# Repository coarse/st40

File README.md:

# ST40 PCB

No frills, open source 40% ortholinear keyboard PCB

## Specs

- Planck-like layout
- South-facing LED (even though there is no backlight) because that's how switches were meant to be oriented
- No backlight, no underglow
- No fancy ESD protection
- No fancy reset circuit
- USB Mini because literally no frills
- STM32F072CBT6

## Requirements

- KiCad 5.0.1
- Default KiCad Schematic Library
- ai03's Switch Footprint Library (included as submodule)

## Notes

1. To be used as a reference for STM32F072CBT6 only
2. Can't guarantee that this PCB is compatible with Planck cases

## Questions?

 - Hit me up on Discord (Miyo#2210) or via e-mail (mfmayol@up.edu.ph)
 
## License

The design is licensed under [CC BY-SA 4.0](https://creativecommons.org/licenses/by-sa/4.0/).

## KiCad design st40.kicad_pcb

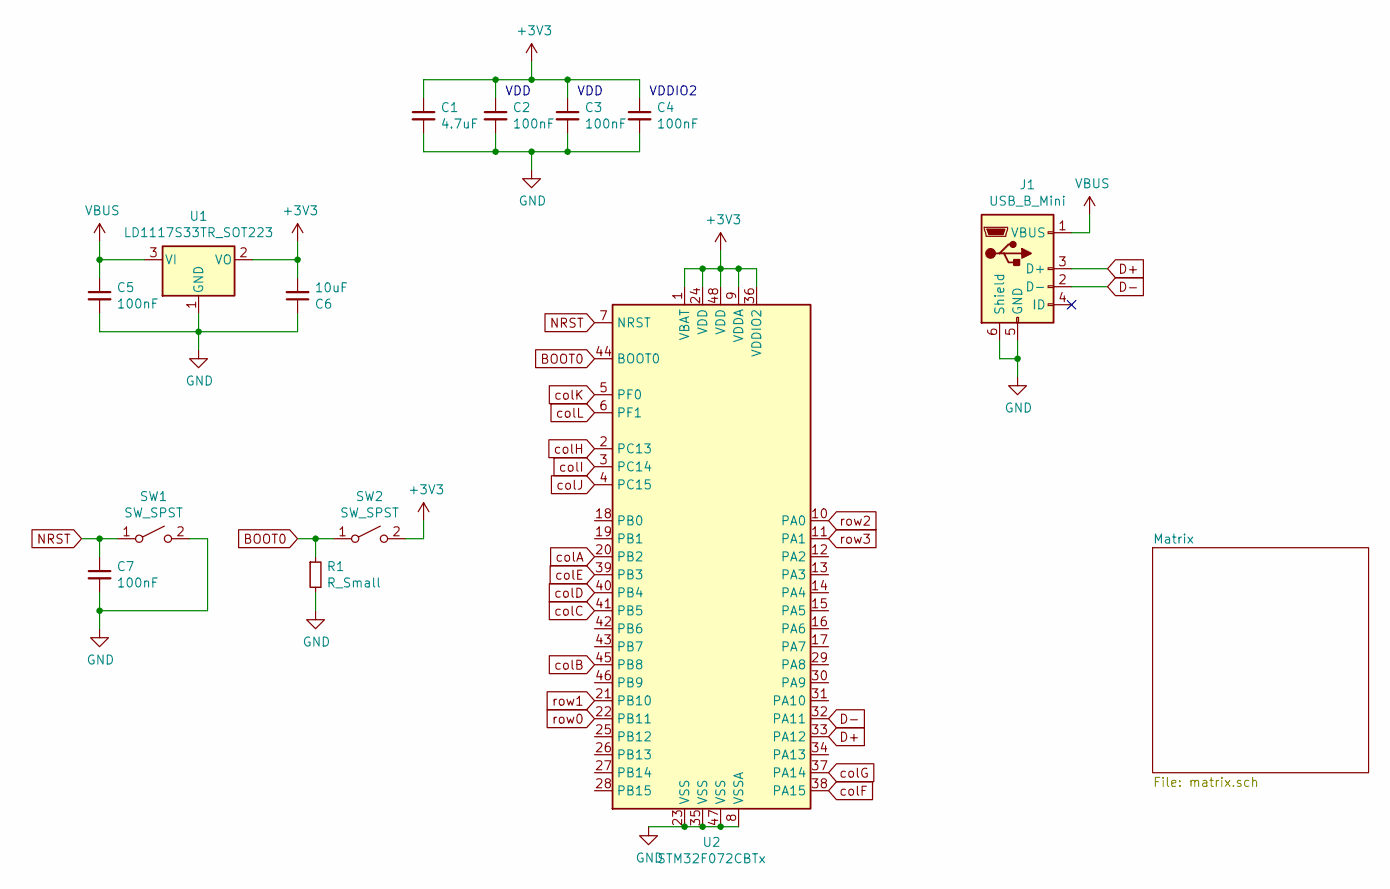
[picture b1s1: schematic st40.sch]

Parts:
C1: 4.7uF; C_0603_1608Metric_Pad1.05x0.95mm_HandSolder
C2, C3, C4, C5, C7: 100nF; C_0603_1608Metric_Pad1.05x0.95mm_HandSolder
C6: 10uF; C_0603_1608Metric_Pad1.05x0.95mm_HandSolder
J1: USB_B_Mini; USB-Mini-B_ LCSC-C46398
R1: R_Small; R_0603_1608Metric_Pad1.05x0.95mm_HandSolder
SW1, SW2: SW_SPST; SW_PUSH_6mm
U1: LD1117S33TR_SOT223; SOT-223
U2: STM32F072CBTx; LQFP-48_7x7mm_P0.5mm

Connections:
+3V3: C1.1, C2.1, C3.1, C4.1, C6.2, SW2.2 (B), U1.2 (VO), U2.1 (VBAT), U2.9 (VDDA), U2.24 (VDD), U2.36 (VDDIO2), U2.48 (VDD)
BOOT0: R1.1, SW2.1 (A), U2.44 (BOOT0)
D+: J1.3 (D+), U2.33 (PA12)
D-: J1.2 (D-), U2.32 (PA11)
GND: C1.2, C2.2, C3.2, C4.2, C5.2, C6.1, C7.2, J1.5 (GND), J1.6 (Shield), R1.2, SW1.2 (B), U1.1 (GND), U2.8 (VSSA), U2.23 (VSS), U2.35 (VSS), U2.47 (VSS)
NRST: C7.1, SW1.1 (A), U2.7 (NRST)
VBUS: C5.1, J1.1 (VBUS), U1.3 (VI)
colA: U2.20 (PB2); also elsewhere on the board
colB: U2.45 (PB8); also elsewhere on the board
colC: U2.41 (PB5); also elsewhere on the board
colD: U2.40 (PB4); also elsewhere on the board
colE: U2.39 (PB3); also elsewhere on the board
colF: U2.38 (PA15); also elsewhere on the board
colG: U2.37 (PA14); also elsewhere on the board
colH: U2.2 (PC13); also elsewhere on the board
colI: U2.3 (PC14); also elsewhere on the board
colJ: U2.4 (PC15); also elsewhere on the board
colK: U2.5 (PF0); also elsewhere on the board
colL: U2.6 (PF1); also elsewhere on the board
row0: U2.22 (PB11); also elsewhere on the board
row1: U2.21 (PB10); also elsewhere on the board
row2: U2.10 (PA0); also elsewhere on the board
row3: U2.11 (PA1); also elsewhere on the board

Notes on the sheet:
VDD
VDDIO2

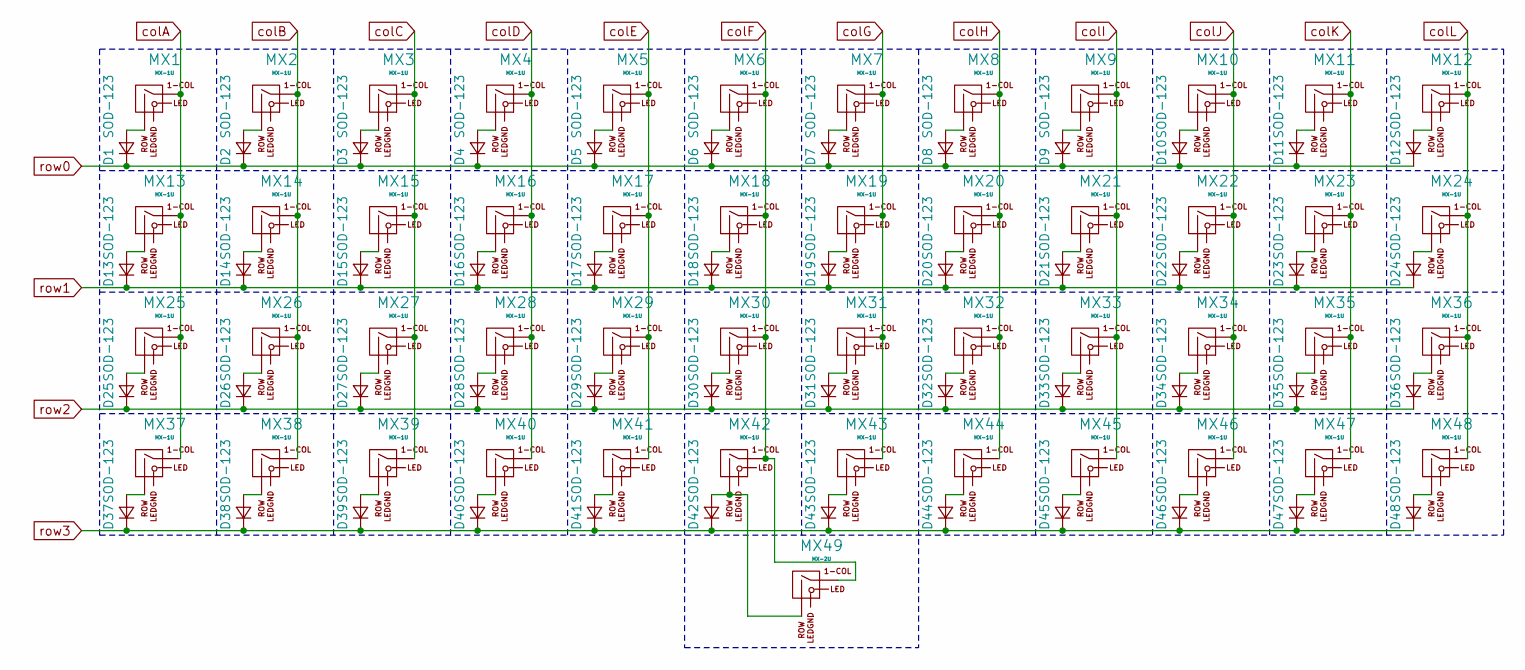
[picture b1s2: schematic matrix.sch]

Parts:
D1, D2, D3, D4, D5, D6, D7, D8, D9, D10, D11, D12, D13, D14, D15, D16, D17, D18, D19, D20, D21, D22, D23, D24, D25, D26, D27, D28, D29, D30, D31, D32, D33, D34, D35, D36, D37, D38, D39, D40, D41, D42, D43, D44, D45, D46, D47, D48: SOD-123; D_SOD-123
MX1, MX2, MX3, MX4, MX5, MX6, MX7, MX8, MX9, MX10, MX11, MX12, MX13, MX14, MX15, MX16, MX17, MX18, MX19, MX20, MX21, MX22, MX23, MX24, MX25, MX26, MX27, MX28, MX29, MX30, MX31, MX32, MX33, MX34, MX35, MX36, MX37, MX38, MX39, MX40, MX41, MX42, MX43, MX44, MX45, MX46, MX47, MX48: MX-1U; MXOnly-1U-NoLED
MX49: MX-2U; MXOnly-2U-ReversedStabilizers-NoLED

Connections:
unnamed: D1.2 (A), MX1.2 (ROW)
unnamed: D2.2 (A), MX2.2 (ROW)
unnamed: D3.2 (A), MX3.2 (ROW)
unnamed: D4.2 (A), MX4.2 (ROW)
unnamed: D5.2 (A), MX5.2 (ROW)
unnamed: D6.2 (A), MX6.2 (ROW)
unnamed: D7.2 (A), MX7.2 (ROW)
unnamed: D8.2 (A), MX8.2 (ROW)
unnamed: D9.2 (A), MX9.2 (ROW)
unnamed: D10.2 (A), MX10.2 (ROW)
unnamed: D11.2 (A), MX11.2 (ROW)
unnamed: D12.2 (A), MX12.2 (ROW)
unnamed: D13.2 (A), MX13.2 (ROW)
unnamed: D14.2 (A), MX14.2 (ROW)
unnamed: D15.2 (A), MX15.2 (ROW)
unnamed: D16.2 (A), MX16.2 (ROW)
unnamed: D17.2 (A), MX17.2 (ROW)
unnamed: D18.2 (A), MX18.2 (ROW)
unnamed: D19.2 (A), MX19.2 (ROW)
unnamed: D20.2 (A), MX20.2 (ROW)
unnamed: D21.2 (A), MX21.2 (ROW)
unnamed: D22.2 (A), MX22.2 (ROW)
unnamed: D23.2 (A), MX23.2 (ROW)
unnamed: D24.2 (A), MX24.2 (ROW)
unnamed: D25.2 (A), MX25.2 (ROW)
unnamed: D26.2 (A), MX26.2 (ROW)
unnamed: D27.2 (A), MX27.2 (ROW)
unnamed: D28.2 (A), MX28.2 (ROW)
unnamed: D29.2 (A), MX29.2 (ROW)
unnamed: D30.2 (A), MX30.2 (ROW)
unnamed: D31.2 (A), MX31.2 (ROW)
unnamed: D32.2 (A), MX32.2 (ROW)
unnamed: D33.2 (A), MX33.2 (ROW)
unnamed: D34.2 (A), MX34.2 (ROW)
unnamed: D35.2 (A), MX35.2 (ROW)
unnamed: D36.2 (A), MX36.2 (ROW)
unnamed: D37.2 (A), MX37.2 (ROW)
unnamed: D38.2 (A), MX38.2 (ROW)
unnamed: D39.2 (A), MX39.2 (ROW)
unnamed: D40.2 (A), MX40.2 (ROW)
unnamed: D41.2 (A), MX41.2 (ROW)
unnamed: D42.2 (A), MX42.2 (ROW), MX49.2 (ROW)
unnamed: D43.2 (A), MX43.2 (ROW)
unnamed: D44.2 (A), MX44.2 (ROW)
unnamed: D45.2 (A), MX45.2 (ROW)
unnamed: D46.2 (A), MX46.2 (ROW)
unnamed: D47.2 (A), MX47.2 (ROW)
unnamed: D48.2 (A), MX48.2 (ROW)
colA: MX1.1 (COL), MX13.1 (COL), MX25.1 (COL), MX37.1 (COL); also elsewhere on the board
colB: MX2.1 (COL), MX14.1 (COL), MX26.1 (COL), MX38.1 (COL); also elsewhere on the board
colC: MX3.1 (COL), MX15.1 (COL), MX27.1 (COL), MX39.1 (COL); also elsewhere on the board
colD: MX4.1 (COL), MX16.1 (COL), MX28.1 (COL), MX40.1 (COL); also elsewhere on the board
colE: MX5.1 (COL), MX17.1 (COL), MX29.1 (COL), MX41.1 (COL); also elsewhere on the board
colF: MX6.1 (COL), MX18.1 (COL), MX30.1 (COL), MX42.1 (COL), MX49.1 (COL); also elsewhere on the board
colG: MX7.1 (COL), MX19.1 (COL), MX31.1 (COL), MX43.1 (COL); also elsewhere on the board
colH: MX8.1 (COL), MX20.1 (COL), MX32.1 (COL), MX44.1 (COL); also elsewhere on the board
colI: MX9.1 (COL), MX21.1 (COL), MX33.1 (COL), MX45.1 (COL); also elsewhere on the board
colJ: MX10.1 (COL), MX22.1 (COL), MX34.1 (COL), MX46.1 (COL); also elsewhere on the board
colK: MX11.1 (COL), MX23.1 (COL), MX35.1 (COL), MX47.1 (COL); also elsewhere on the board
colL: MX12.1 (COL), MX24.1 (COL), MX36.1 (COL), MX48.1 (COL); also elsewhere on the board
row0: D1.1 (K), D2.1 (K), D3.1 (K), D4.1 (K), D5.1 (K), D6.1 (K), D7.1 (K), D8.1 (K), D9.1 (K), D10.1 (K), D11.1 (K), D12.1 (K); also elsewhere on the board
row1: D13.1 (K), D14.1 (K), D15.1 (K), D16.1 (K), D17.1 (K), D18.1 (K), D19.1 (K), D20.1 (K), D21.1 (K), D22.1 (K), D23.1 (K), D24.1 (K); also elsewhere on the board
row2: D25.1 (K), D26.1 (K), D27.1 (K), D28.1 (K), D29.1 (K), D30.1 (K), D31.1 (K), D32.1 (K), D33.1 (K), D34.1 (K), D35.1 (K), D36.1 (K); also elsewhere on the board
row3: D37.1 (K), D38.1 (K), D39.1 (K), D40.1 (K), D41.1 (K), D42.1 (K), D43.1 (K), D44.1 (K), D45.1 (K), D46.1 (K), D47.1 (K), D48.1 (K); also elsewhere on the board

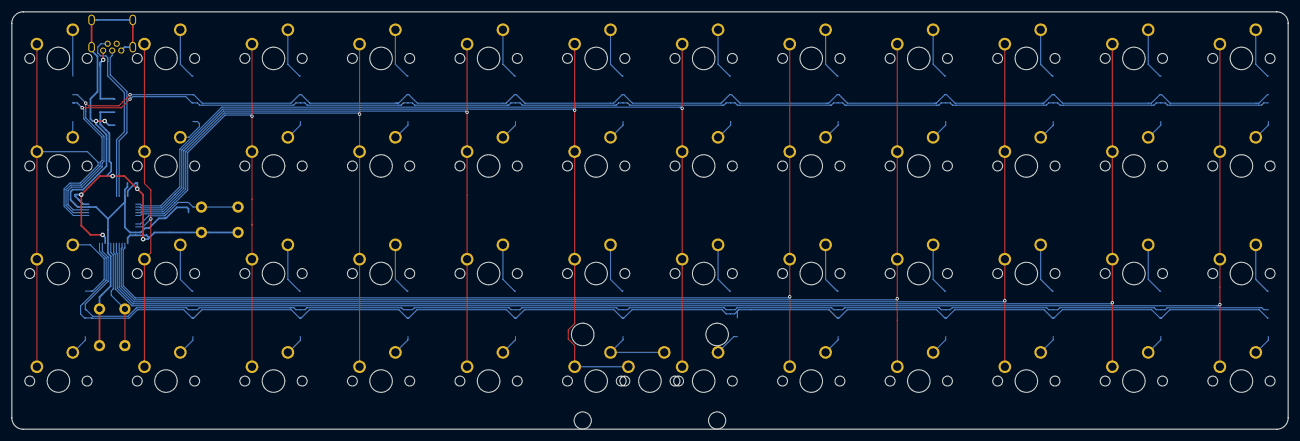
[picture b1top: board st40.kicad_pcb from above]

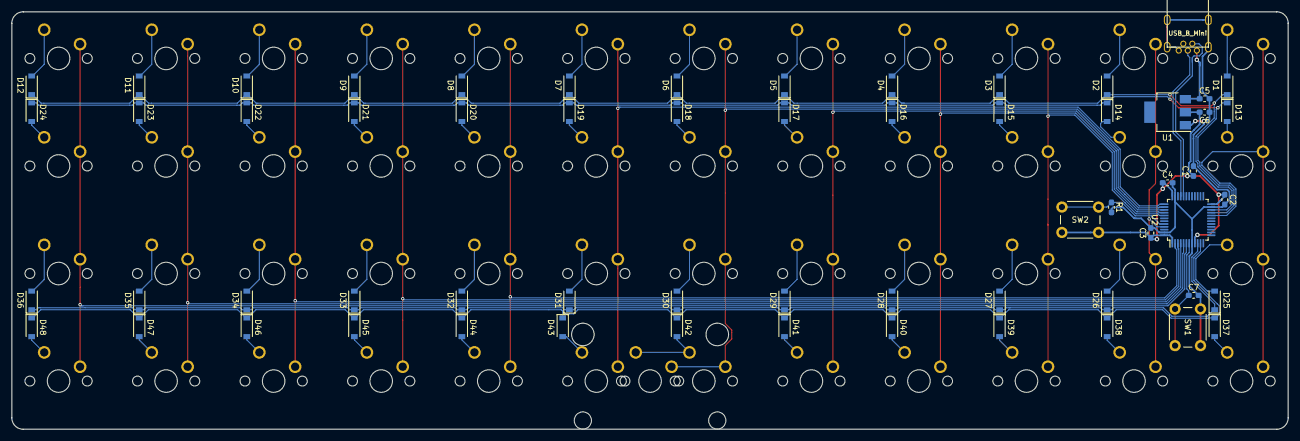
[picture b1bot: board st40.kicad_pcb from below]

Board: 2 copper layers, 226.1 x 73.9 mm, 110 parts (61 on the bottom side), 71 nets.

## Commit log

2019-02-18 initial and probably final commit
2019-02-18 fixed missing traces from col/rows to mcu, did some rerouting, fixed board outline
2019-02-18 moved diode placement
2019-02-18 add shameless ad for my services
2019-02-18 add render
2019-02-18 link image
2019-03-13 Create LICENSE
